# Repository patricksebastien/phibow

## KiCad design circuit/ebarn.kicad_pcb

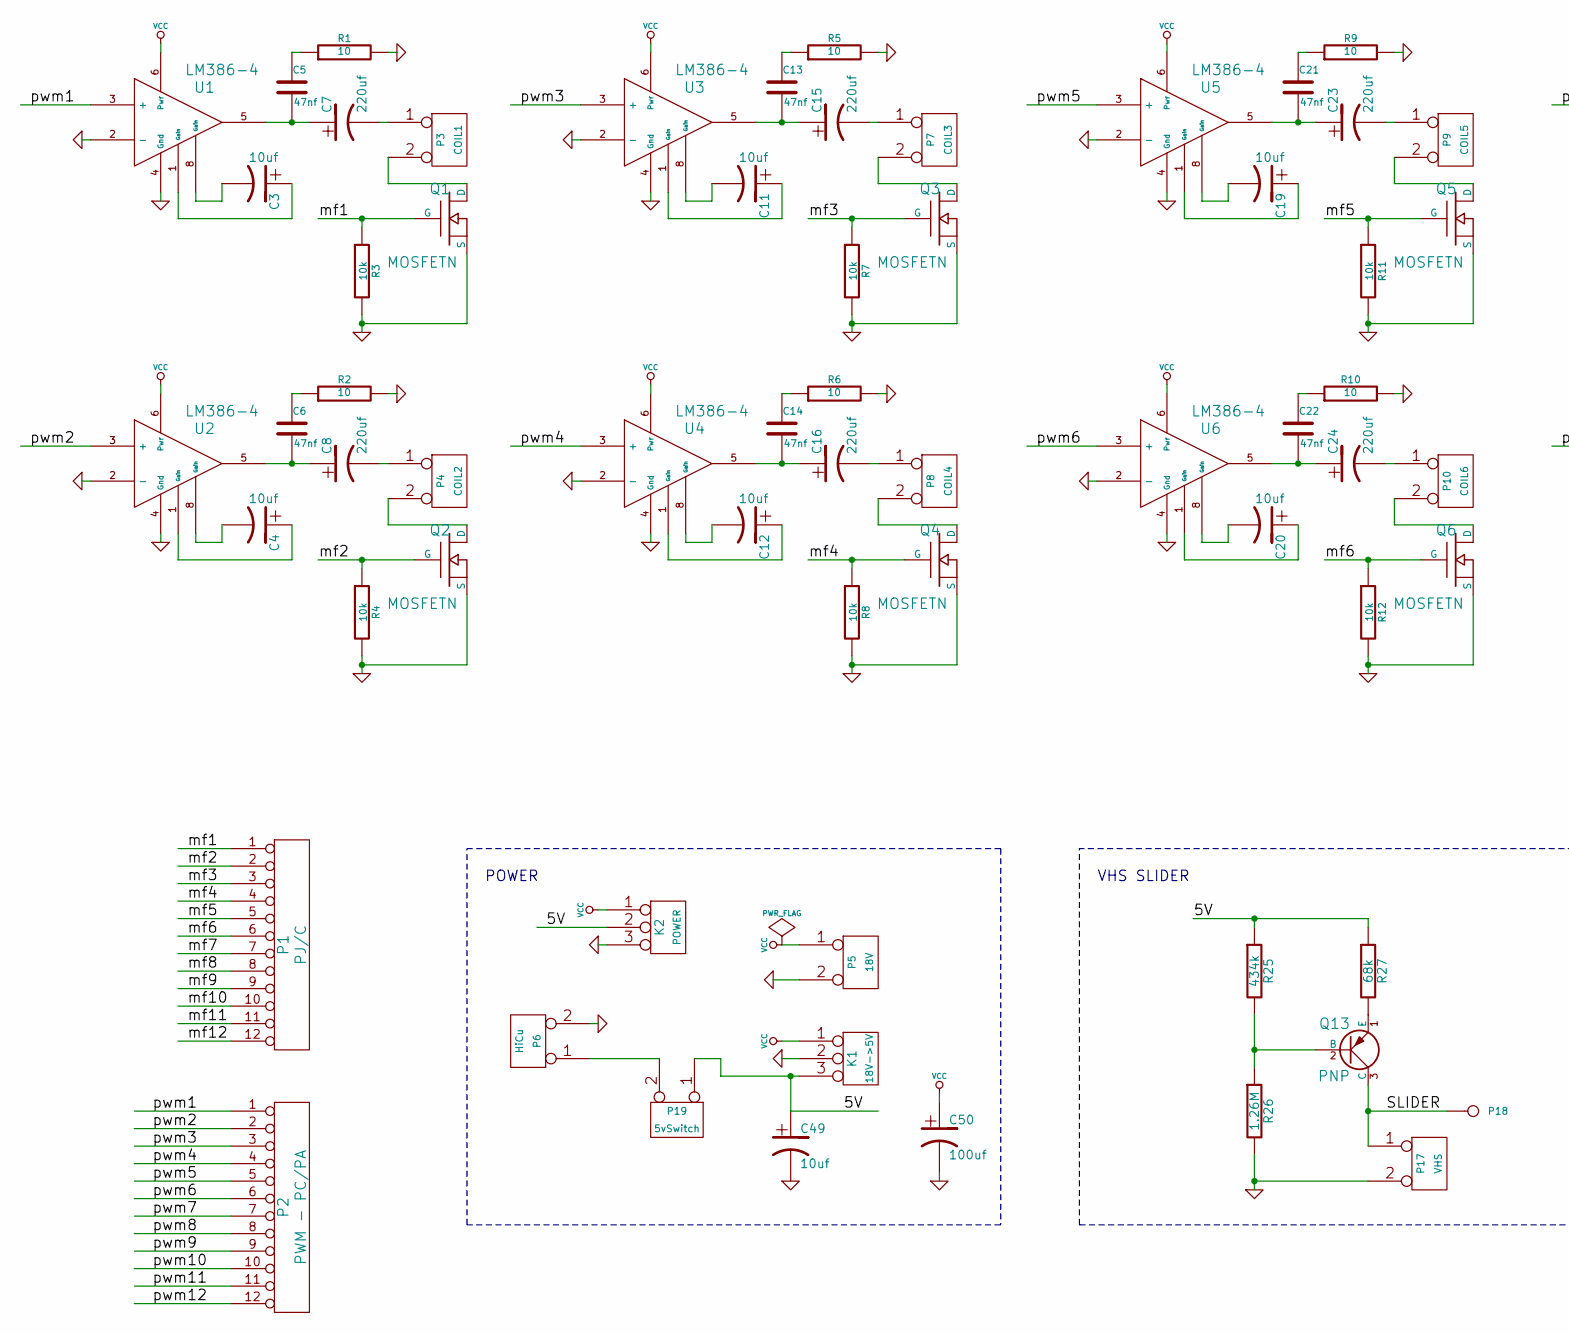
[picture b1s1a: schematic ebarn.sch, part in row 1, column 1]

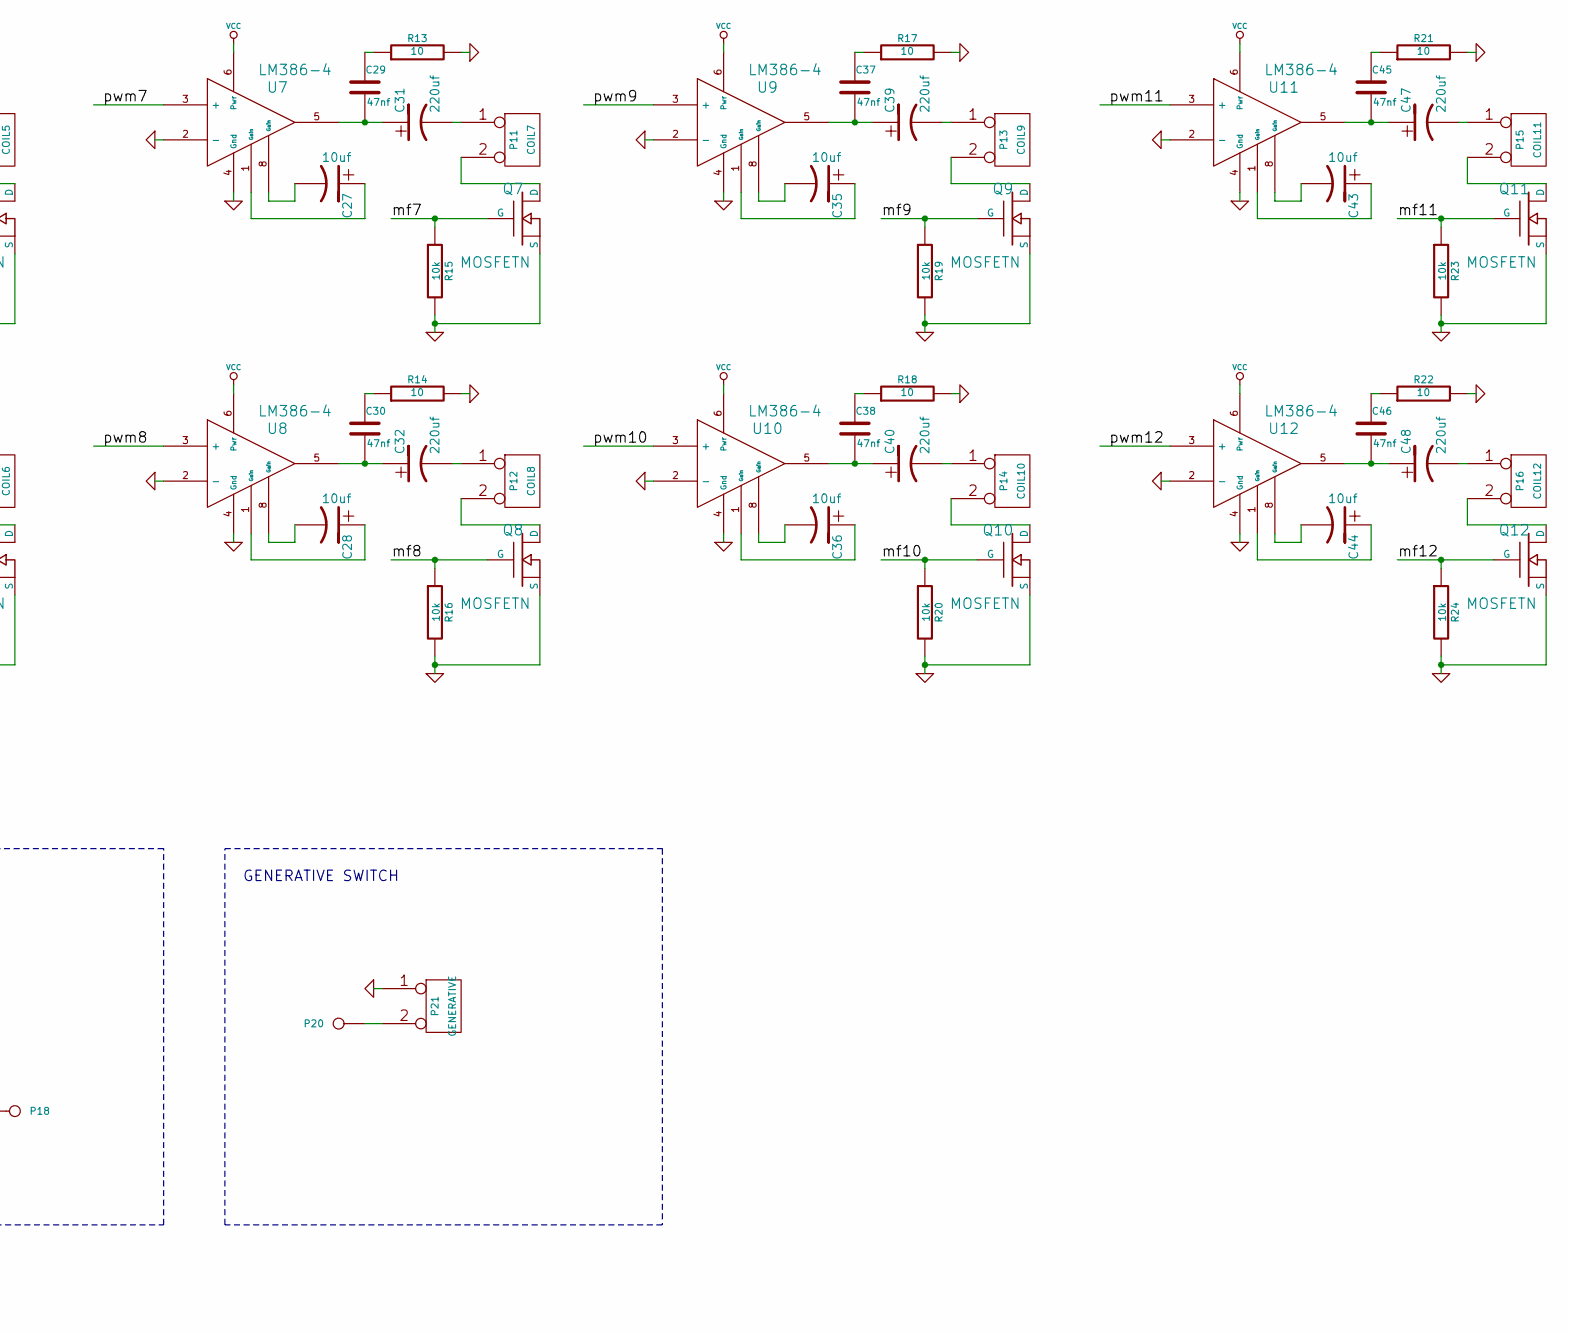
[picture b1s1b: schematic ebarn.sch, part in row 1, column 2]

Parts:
C3, C4, C11, C12, C19, C20, C27, C28, C35, C36, C43, C44, C49: 10uf
C5, C6, C13, C14, C21, C22, C29, C30, C37, C38, C45, C46: 47nf
C7, C8, C15, C16, C23, C24, C31, C32, C39, C40, C47, C48: 220uf
C50: 100uf
K1: 18V->5V
K2: POWER
P1: PJ/C
P2: PWM - PC/PA
P3: COIL1
P4: COIL2
P5: 18V
P6: HiCu
P7: COIL3
P8: COIL4
P9: COIL5
P10: COIL6
P11: COIL7
P12: COIL8
P13: COIL9
P14: COIL10
P15: COIL11
P16: COIL12
P17: VHS
P18, P20: CONN_1
P19: 5vSwitch
P21: GENERATIVE
Q1, Q2, Q3, Q4, Q5, Q6, Q7, Q8, Q9, Q10, Q11, Q12: MOSFETN
Q13: PNP
R1, R2, R5, R6, R9, R10, R13, R14, R17, R18, R21, R22: 10
R3, R4, R7, R8, R11, R12, R15, R16, R19, R20, R23, R24: 10k
R25: 434k
R26: 1.26M
R27: 68k
U1, U2, U3, U4, U5, U6, U7, U8, U9, U10, U11, U12: LM386-4

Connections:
/5V: C49.1, K1.3, K2.2 (PM), P19.1, R25.1, R27.1; also elsewhere on the board
/SLIDER: P17.1, P18.1, Q13.3 (C)
/mf1: P1.1, Q1.G, R3.1
/mf2: P1.2, Q2.G, R4.1
/mf3: P1.3, Q3.G, R7.1
/mf4: P1.4, Q4.G, R8.1
/mf5: P1.5, Q5.G, R11.1
/mf6: P1.6, Q6.G, R12.1
/mf7: P1.7, Q7.G, R15.1
/mf8: P1.8, Q8.G, R16.1
/mf9: P1.9, Q9.G, R19.1
/mf10: P1.10, Q10.G, R20.1
/mf11: P1.11, Q11.G, R23.1
/mf12: P1.12, Q12.G, R24.1
/pwm1: P2.1, U1.3 (+)
/pwm2: P2.2, U2.3 (+)
/pwm3: P2.3, U3.3 (+)
/pwm4: P2.4, U4.3 (+)
/pwm5: P2.5, U5.3 (+)
/pwm6: P2.6, U6.3 (+)
/pwm7: P2.7, U7.3 (+)
/pwm8: P2.8, U8.3 (+)
/pwm9: P2.9, U9.3 (+)
/pwm10: P2.10, U10.3 (+)
/pwm11: P2.11, U11.3 (+)
/pwm12: P2.12, U12.3 (+)
GND: C49.2, C50.2, K1.2 (PM), K2.3, P5.2 (PM), P6.2 (PM), P17.2 (PM), P21.1, Q1.S, Q2.S, Q3.S, Q4.S, Q5.S, Q6.S, Q7.S, Q8.S, Q9.S, Q10.S, Q11.S, Q12.S, R1.2, R2.2, R3.2, R4.2, R5.2, R6.2, R7.2, R8.2, R9.2, R10.2, R11.2, R12.2, R13.2, R14.2, R15.2, R16.2, R17.2, R18.2, R19.2, R20.2, R21.2, R22.2, R23.2, R24.2, R26.2, U1.2 (-), U1.4 (Gnd), U2.2 (-), U2.4 (Gnd), U3.2 (-), U3.4 (Gnd), U4.2 (-), U4.4 (Gnd), U5.2 (-), U5.4 (Gnd), U6.2 (-), U6.4 (Gnd), U7.2 (-), U7.4 (Gnd), U8.2 (-), U8.4 (Gnd), U9.2 (-), U9.4 (Gnd), U10.2 (-), U10.4 (Gnd), U11.2 (-), U11.4 (Gnd), U12.2 (-), U12.4 (Gnd)
unnamed: P9.2 (PM), Q5.D
unnamed: C19.1, U5.1 (Gain)
unnamed: C19.2, U5.8 (Gain)
unnamed: C21.2, C23.1, U5.5
unnamed: C12.1, U4.1 (Gain)
unnamed: C23.2, P9.1
unnamed: C12.2, U4.8 (Gain)
unnamed: C14.2, C16.1, U4.5
unnamed: C14.1, R6.1
unnamed: C20.2, U6.8 (Gain)
unnamed: C22.2, C24.1, U6.5
unnamed: C22.1, R10.1
unnamed: P11.2 (PM), Q7.D
unnamed: C27.1, U7.1 (Gain)
unnamed: C21.1, R9.1
unnamed: C24.2, P10.1
unnamed: P10.2 (PM), Q6.D
unnamed: C20.1, U6.1 (Gain)
unnamed: P4.2 (PM), Q2.D
unnamed: C4.1, U2.1 (Gain)
unnamed: C3.2, U1.8 (Gain)
unnamed: C5.2, C7.1, U1.5
unnamed: C7.2, P3.1
unnamed: C5.1, R1.1
unnamed: C13.2, C15.1, U3.5
unnamed: C13.1, R5.1
unnamed: P8.2 (PM), Q4.D
unnamed: C16.2, P8.1
unnamed: C4.2, U2.8 (Gain)
unnamed: C6.2, C8.1, U2.5
unnamed: C8.2, P4.1
unnamed: C6.1, R2.1
unnamed: C15.2, P7.1
unnamed: P7.2 (PM), Q3.D
unnamed: C11.1, U3.1 (Gain)
unnamed: C43.2, U11.8 (Gain)
unnamed: C45.2, C47.1, U11.5
unnamed: C45.1, R21.1
unnamed: P16.2 (PM), Q12.D
unnamed: C36.2, U10.8 (Gain)
unnamed: C38.2, C40.1, U10.5
unnamed: C38.1, R18.1
unnamed: C44.1, U12.1 (Gain)
unnamed: C47.2, P15.1
unnamed: P15.2 (PM), Q11.D
unnamed: C43.1, U11.1 (Gain)
unnamed: P20.1, P21.2 (PM)
unnamed: P6.1, P19.2 (PM)
unnamed: C44.2, U12.8 (Gain)
unnamed: C46.2, C48.1, U12.5
unnamed: C48.2, P16.1
unnamed: C46.1, R22.1
unnamed: C28.1, U8.1 (Gain)
unnamed: C28.2, U8.8 (Gain)
unnamed: C30.2, C32.1, U8.5
unnamed: C30.1, R14.1
unnamed: C31.2, P11.1
unnamed: C27.2, U7.8 (Gain)
unnamed: C29.2, C31.1, U7.5
unnamed: C29.1, R13.1
unnamed: C32.2, P12.1
unnamed: P12.2 (PM), Q8.D
unnamed: C40.2, P14.1
unnamed: P14.2 (PM), Q10.D
unnamed: C37.2, C39.1, U9.5
unnamed: C36.1, U10.1 (Gain)
unnamed: C39.2, P13.1
unnamed: P13.2 (PM), Q9.D
unnamed: C35.2, U9.8 (Gain)
unnamed: C37.1, R17.1
unnamed: C11.2, U3.8 (Gain)
unnamed: C3.1, U1.1 (Gain)
unnamed: P3.2 (PM), Q1.D
unnamed: Q13.2 (B), R25.2, R26.1
unnamed: Q13.1 (E), R27.2
unnamed: C35.1, U9.1 (Gain)
VCC: C50.1, K1.1, K2.1, P5.1, U1.6 (Pwr), U2.6 (Pwr), U3.6 (Pwr), U4.6 (Pwr), U5.6 (Pwr), U6.6 (Pwr), U7.6 (Pwr), U8.6 (Pwr), U9.6 (Pwr), U10.6 (Pwr), U11.6 (Pwr), U12.6 (Pwr)

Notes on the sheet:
VHS SLIDER
POWER
GENERATIVE SWITCH

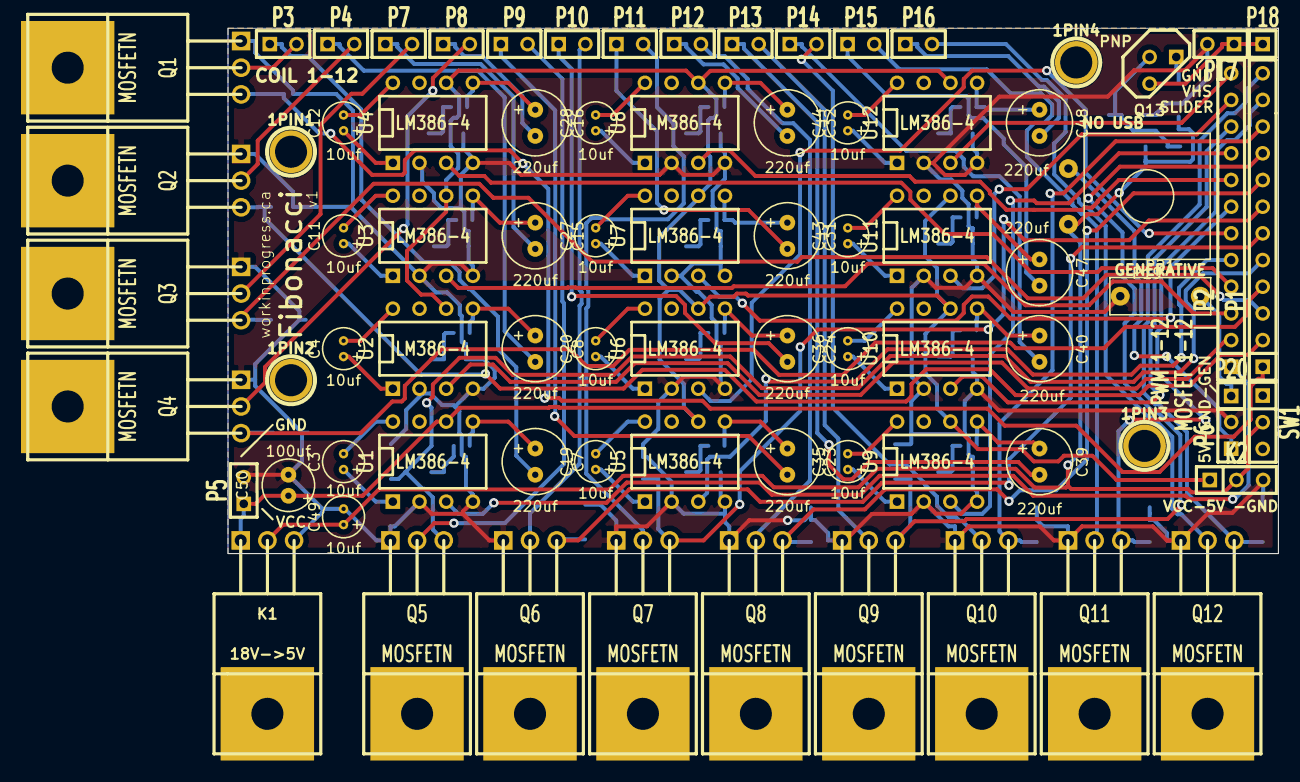
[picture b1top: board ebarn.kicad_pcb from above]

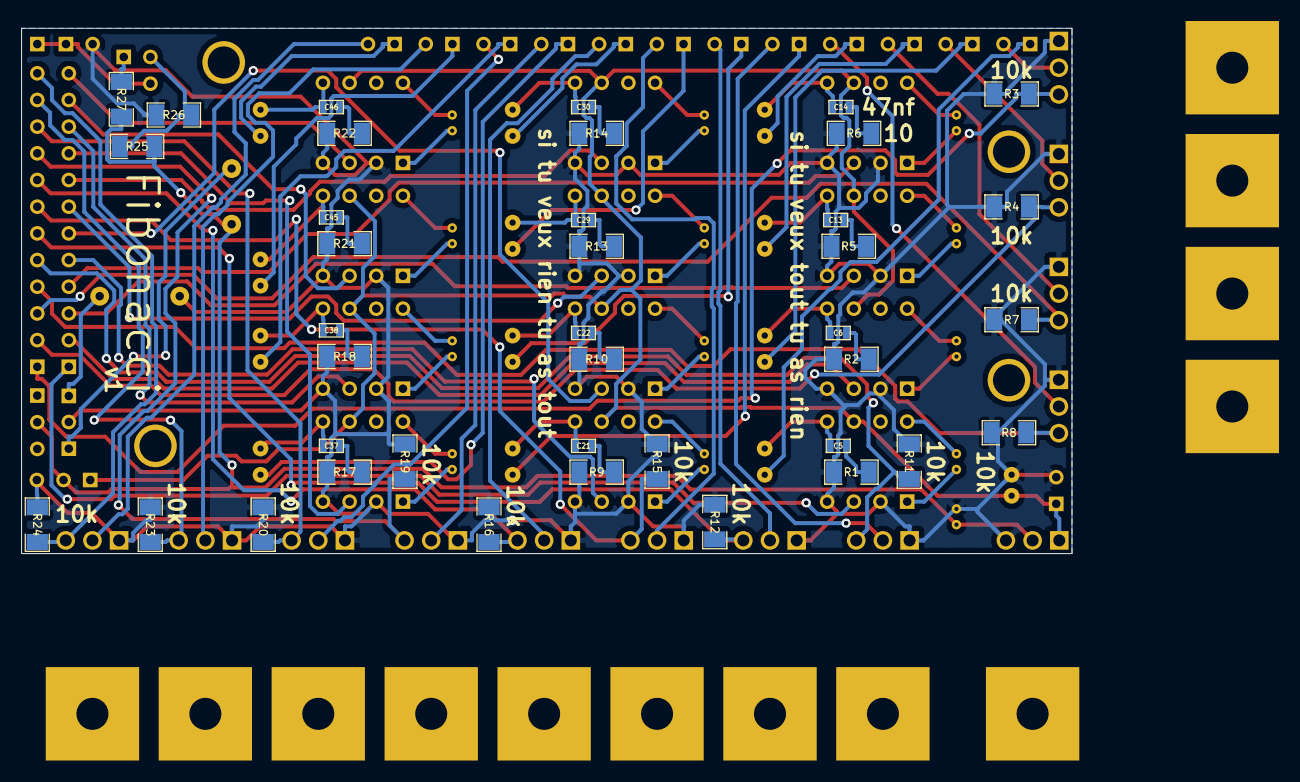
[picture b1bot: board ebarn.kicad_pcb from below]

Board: 2 copper layers, 100.0 x 50.0 mm, 118 parts (39 on the bottom side), 104 nets.

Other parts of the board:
1PIN1: P1; 1pin
1PIN2: P2; 1pin
1PIN3: P3; 1pin
1PIN4: P4; 1pin
SW1: SWITCH_INV; SIL-3

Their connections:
/5V: SW1.2; also elsewhere on the board

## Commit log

2019-01-07 initial release
